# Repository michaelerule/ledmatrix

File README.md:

# LED matrix

Files related to hobby LED matrix display projects.

### License

Unless otherwise specified, media, text, and rendered outputs are licensed under the [Creative Commons Attribution Share Alike 4.0 license](https://choosealicense.com/licenses/cc-by-sa-4.0/) (CC BY-SA 4.0). Source code is licensed under the [GNU General Public License version 3.0](https://www.gnu.org/copyleft/gpl.html) (GPLv3). The CC BY-SA 4.0 is [one-way compatible](https://creativecommons.org/compatiblelicenses) with the GPLv3 license. 
This license does not apply to the project as a whole, but only to those modules or functions for which an alternative license is not otherwise specified.

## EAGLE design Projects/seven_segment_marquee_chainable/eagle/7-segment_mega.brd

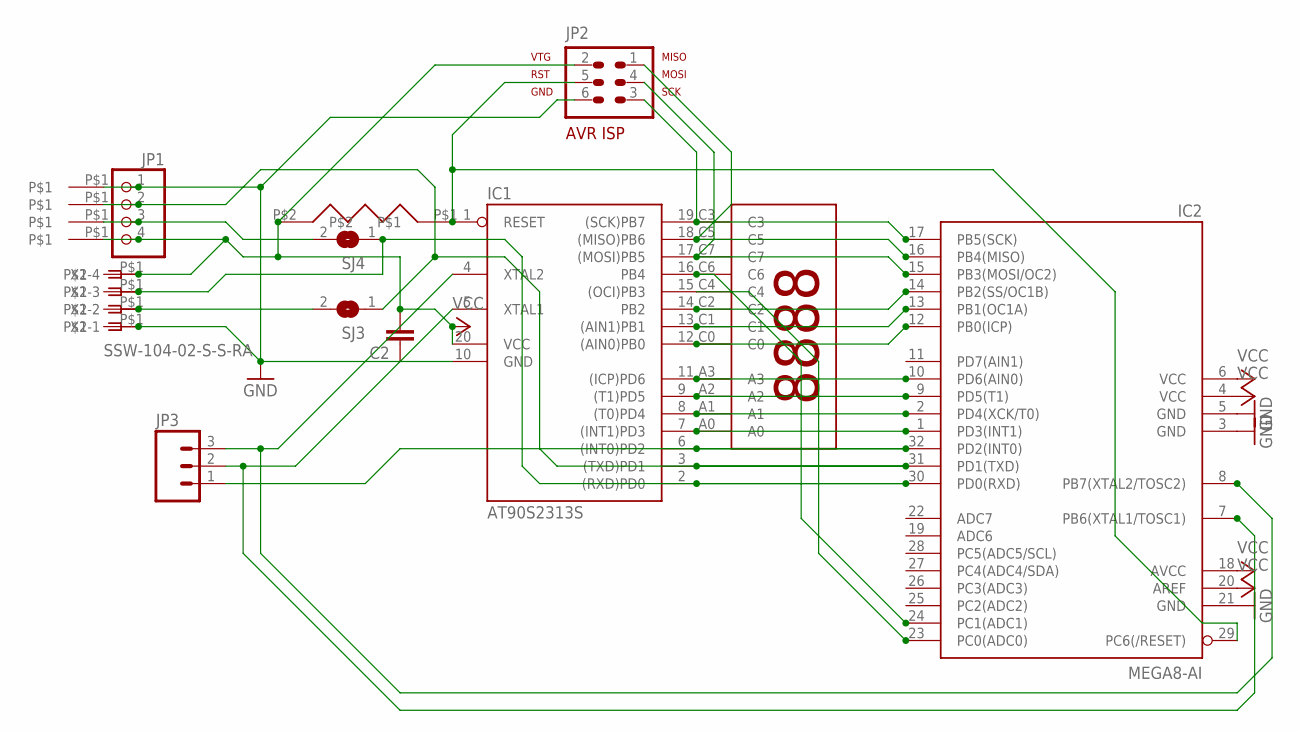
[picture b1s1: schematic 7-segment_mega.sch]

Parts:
C2: CAPPTH; CAP-PTH-SMALL
IC1: AT90S2313S; SO20L
IC2: MEGA8-AI; TQFP32-08
JP1: PINHD-1X4/90; 1X04/90
JP2: AVR-ISP-6
JP3: M03PTH; 1X03
SJ3, SJ4: SJ
U$1: 7-SEGMENT-DISPLAY-5462-BS; 7SEG_5462BS
U$2: R-6
U$3, U$4, U$5, U$6, U$7, U$8, U$9, U$10: WIREPAD_SQUARE_1
X2: SSW-104-02-S-S-RA

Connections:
GND: C2.1, IC1.10 (GND), IC2.3 (GND), IC2.5 (GND), IC2.21 (GND), JP1.1, JP2.6, U$3.P$1, U$10.P$1, X2.1
unnamed: IC1.14 (PB2), IC2.14 (PB2(SS/OC1B)), U$1.C2
unnamed: IC1.17 ((MOSI)PB5), IC2.15 (PB3(MOSI/OC2)), JP2.4, U$1.C7
unnamed: IC1.18 ((MISO)PB6), IC2.16 (PB4(MISO)), JP2.1, U$1.C5
unnamed: IC1.19 ((SCK)PB7), IC2.17 (PB5(SCK)), JP2.3, U$1.C3
unnamed: IC1.11 ((ICP)PD6), IC2.10 (PD6(AIN0)), U$1.A3
unnamed: IC1.7 ((INT1)PD3), IC2.1 (PD3(INT1)), U$1.A0
unnamed: IC1.12 ((AIN0)PB0), IC2.12 (PB0(ICP)), U$1.C0
unnamed: IC1.8 ((T0)PD4), IC2.2 (PD4(XCK/T0)), U$1.A1
unnamed: IC1.9 ((T1)PD5), IC2.9 (PD5(T1)), U$1.A2
unnamed: IC1.13 ((AIN1)PB1), IC2.13 (PB1(OC1A)), U$1.C1
unnamed: SJ3.2, U$9.P$1, X2.2
unnamed: JP1.3, SJ4.2, U$5.P$1
unnamed: IC1.2 ((RXD)PD0), IC2.30 (PD0(RXD)), SJ4.1, U$8.P$1, X2.3
unnamed: IC1.1 (RESET), IC2.29 (PC6(/RESET)), JP2.5, U$2.P$1
unnamed: IC1.3 ((TXD)PD1), IC2.31 (PD1(TXD)), JP1.2, SJ3.1, U$4.P$1
unnamed: IC1.15 ((OCI)PB3), IC2.23 (PC0(ADC0)), U$1.C4
unnamed: IC1.16 (PB4), IC2.24 (PC1(ADC1)), U$1.C6
PD2: IC1.6 ((INT0)PD2), IC2.32 (PD2(INT0)), JP3.1
VCC: C2.2, IC1.20 (VCC), IC2.4 (VCC), IC2.6 (VCC), IC2.18 (AVCC), IC2.20 (AREF), JP1.4, JP2.2, U$2.P$2, U$6.P$1, U$7.P$1, X2.4
XTAL0: IC1.4 (XTAL2), IC2.8 (PB7(XTAL2/TOSC2)), JP3.3
XTAL1: IC1.5 (XTAL1), IC2.7 (PB6(XTAL1/TOSC1)), JP3.2

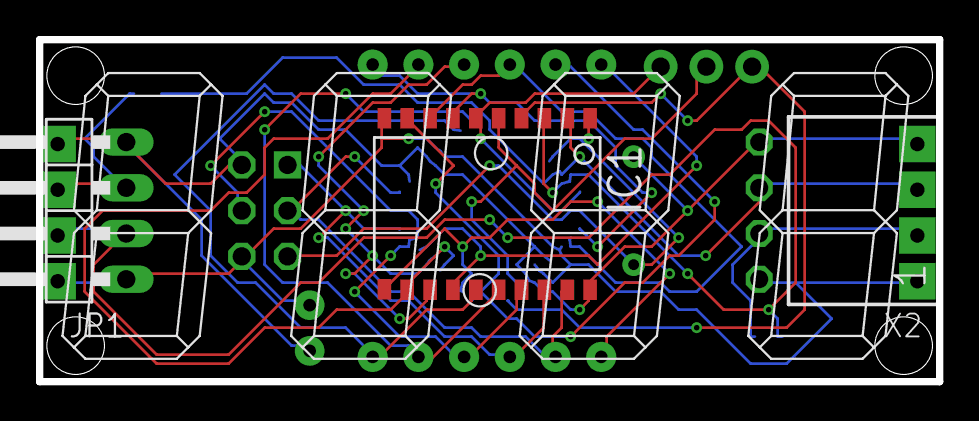
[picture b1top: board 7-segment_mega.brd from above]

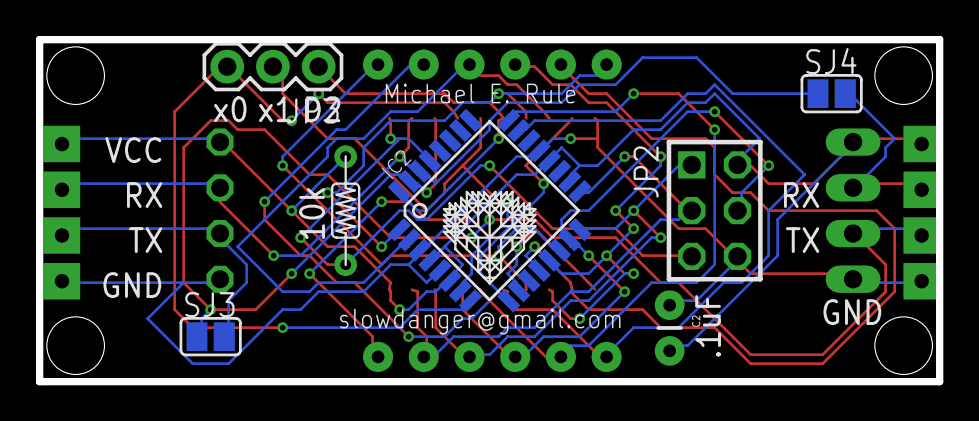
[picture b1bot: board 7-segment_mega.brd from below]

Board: 2 copper layers, 50.0 x 19.0 mm, 20 parts (8 on the bottom side), 22 nets.

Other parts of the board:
U$11: LOGO

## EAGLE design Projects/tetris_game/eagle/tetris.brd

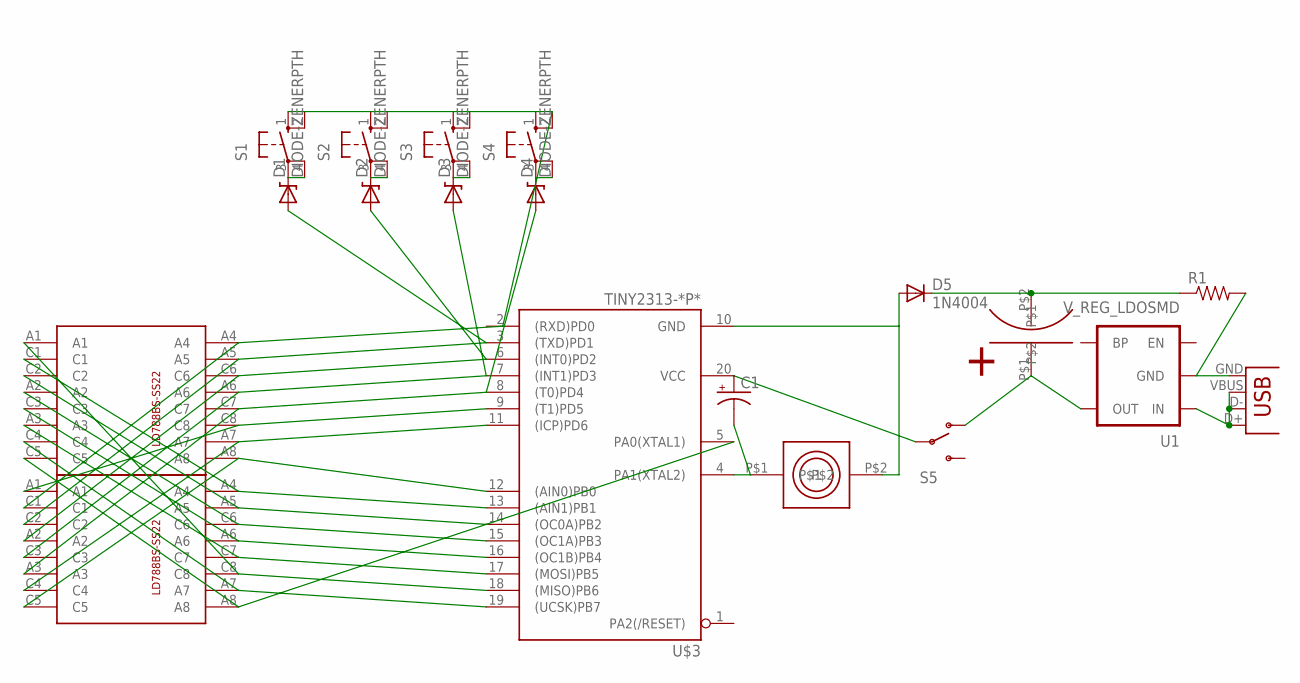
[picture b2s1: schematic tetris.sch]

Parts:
C1: CAP_POLPTH1; CPOL-RADIAL-100UF-25V
D1, D2, D3, D4: DIODE-ZENERPTH; DIODE-ZENER
D5: 1N4004; DO41-10
R1: RESISTORPTH1; AXIAL-0.3
S1, S2, S3, S4: 10-XX; B3F-10XX
S5: SWITCH-SPSTSMD2; SWITCH-SPDT-SMD
U1: V_REG_LDOSMD; SOT23-5
U$1, U$2: LD788BS-SS22
U$3: TINY2313-*P*; DIL20
U$4: I-80450RF; ISK4.1K_I-80450RF_I2G
U$5: NICHICON_12F; NICHICON_10X30
X1: USB-MICROB

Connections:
unnamed: U$1.A4, U$2.C1, U$3.13 ((AIN1)PB1)
unnamed: U$1.A5, U$2.C2, U$3.14 ((OC0A)PB2)
unnamed: U$1.C6, U$2.A2, U$3.15 ((OC1A)PB3)
unnamed: U$1.A6, U$2.C3, U$3.16 ((OC1B)PB4)
unnamed: U$1.C7, U$2.A3, U$3.17 ((MOSI)PB5)
unnamed: U$1.A7, U$2.C4, U$3.19 ((UCSK)PB7)
unnamed: U$1.A8, U$2.C5, U$3.5 (PA0(XTAL1))
unnamed: U$1.C8, U$2.A1, U$3.18 ((MISO)PB6)
unnamed: D5.C, R1.P$1 (1), U$5.P$2
unnamed: D1.P$2 (A), U$1.C2, U$2.A5, U$3.3 ((TXD)PD1)
unnamed: D2.P$2 (A), U$1.A2, U$2.C6, U$3.6 ((INT0)PD2)
unnamed: D3.P$2 (A), U$1.C3, U$2.A6, U$3.7 ((INT1)PD3)
unnamed: D4.P$2 (A), U$1.A3, U$2.C7, U$3.8 ((T0)PD4)
unnamed: U$1.A1, U$2.C8, U$3.9 ((T1)PD5)
unnamed: U$1.C4, U$2.A7, U$3.11 ((ICP)PD6)
unnamed: U$1.C5, U$2.A8, U$3.12 ((AIN0)PB0)
unnamed: C1.2 (-), U$3.4 (PA1(XTAL2)), U$4.P$1
unnamed: D5.A, U$3.10 (GND), U$4.P$2
unnamed: S5.1 (O), U1.5 (OUT), U$5.P$1
unnamed: D1.P$1 (C), S1.3, S1.4 (P1)
unnamed: D2.P$1 (C), S2.3, S2.4 (P1)
unnamed: D3.P$1 (C), S3.3, S3.4 (P1)
unnamed: D4.P$1 (C), S4.3, S4.4 (P1)
unnamed: R1.P$2 (2), U1.2 (GND), X1.GND
unnamed: U1.1 (IN), X1.D+, X1.D-, X1.VBUS
unnamed: C1.1 (+), S5.2, U$3.20 (VCC)
unnamed: S1.1 (S), S1.2 (S1), S2.1 (S), S2.2 (S1), S3.1 (S), S3.2 (S1), S4.1 (S), S4.2 (S1), U$1.C1, U$2.A4

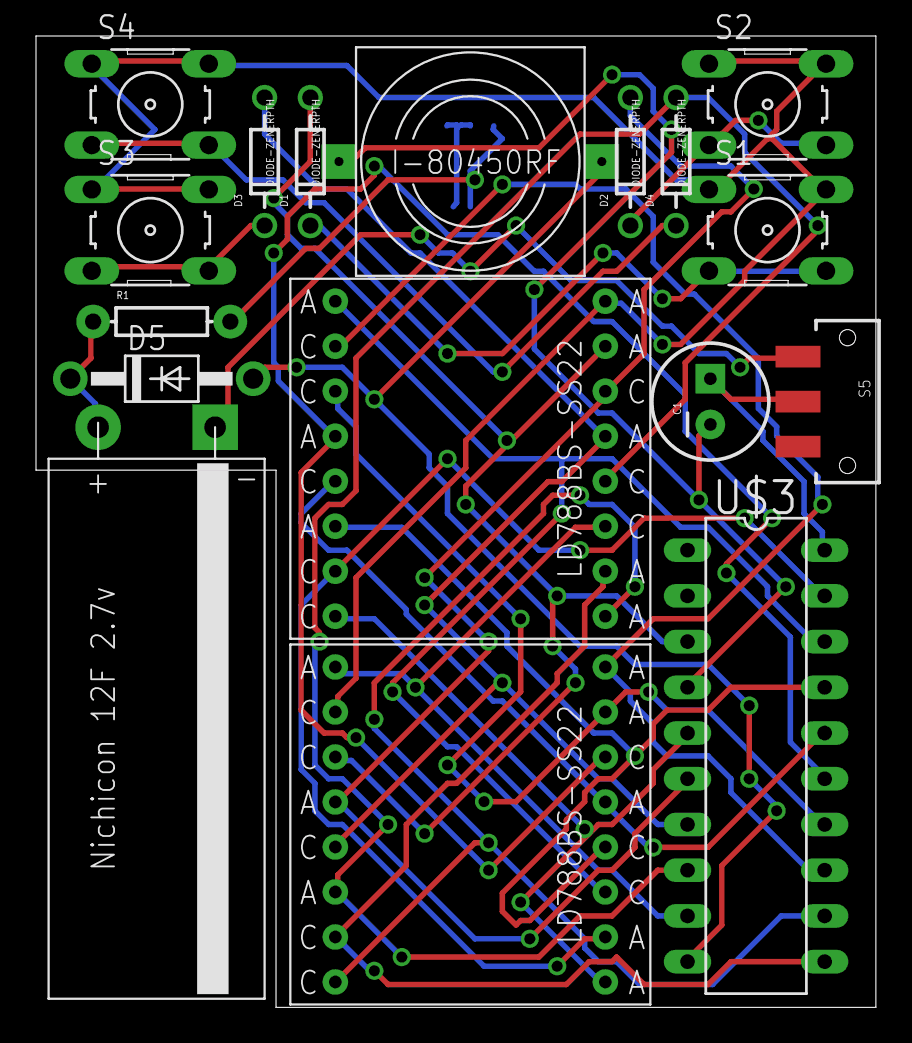
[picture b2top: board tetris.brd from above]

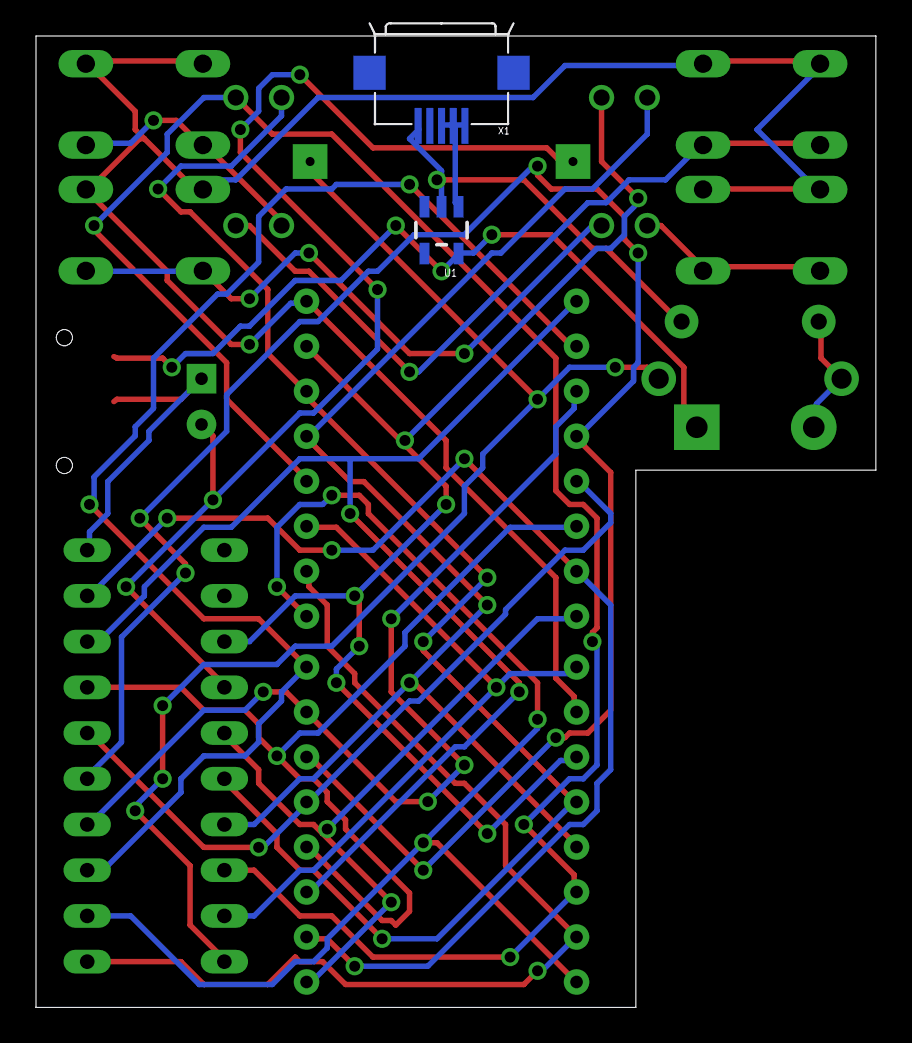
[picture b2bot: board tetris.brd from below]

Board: 2 copper layers, 46.7 x 54.0 mm, 19 parts (2 on the bottom side), 27 nets.

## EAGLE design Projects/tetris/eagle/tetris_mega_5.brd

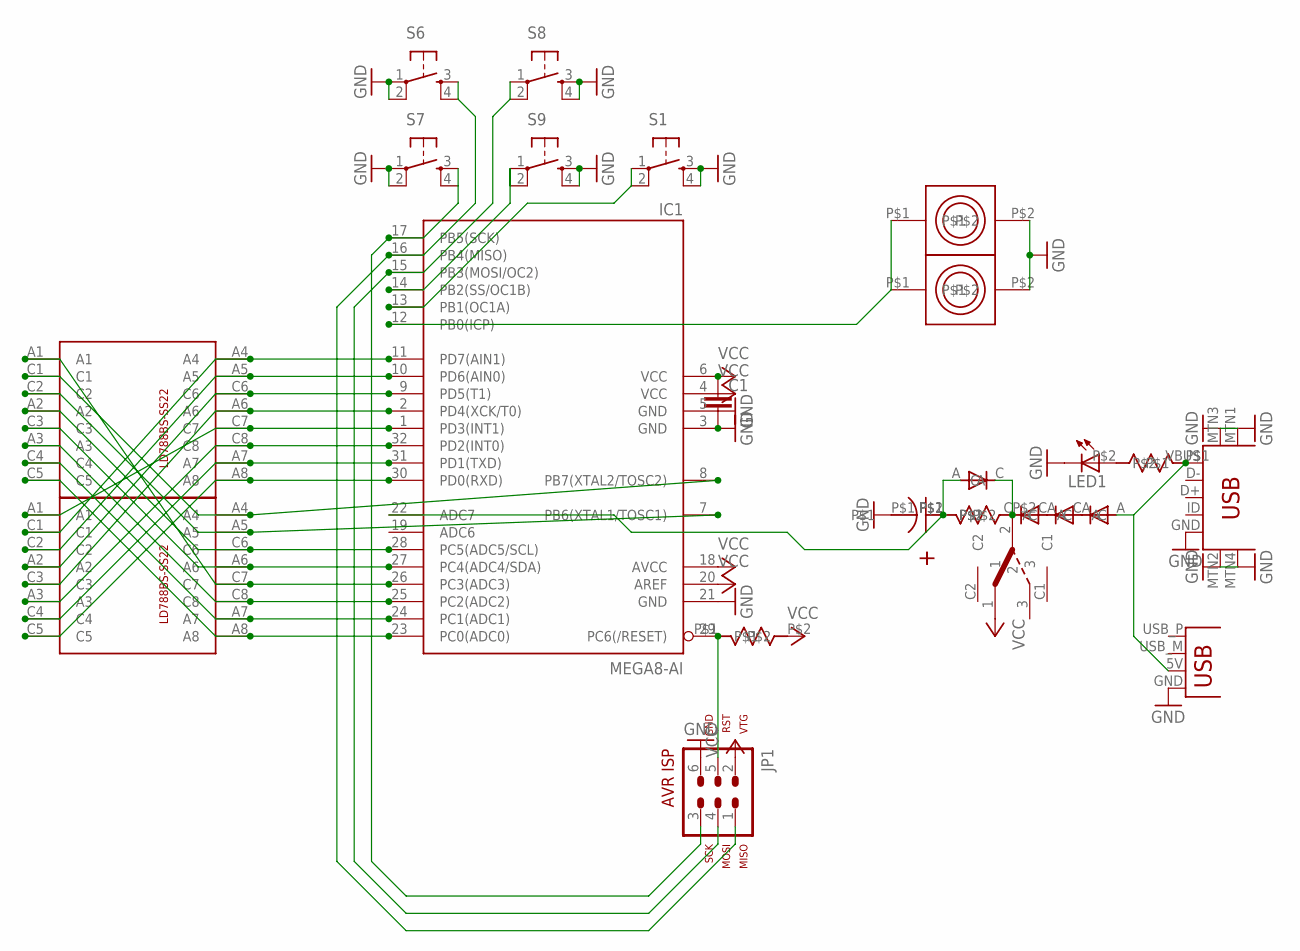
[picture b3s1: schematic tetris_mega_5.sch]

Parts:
C1: CAPPTH; CAP-PTH-SMALL
IC1: MEGA8-AI; TQFP32-08
JP1: AVR-ISP-6R
LED1: LED3MM
S1, S6, S7, S8, S9: TAC_SWITCHPTH; TACTILE-PTH
U$1, U$2: LD788BS-SS22
U$3: PIEZO_ROUND_PTH; PIEZO_ROUND_ENCASED_PTH
U$4: I-80450RF; ISK4.1K_I-80450RF_I2G
U$5: USB-MINIB-5PIN; USB-MINIB
U$6: NICHICON_12F; NICHICON_10X30
U$7, U$11, U$17: R-6
U$8, U$9, U$10, U$12: D-6; D-7.5
U$15: SPST_PTH; SWITCH2
X1: USBPCB; USB-A-PCB

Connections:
GND: C1.2, IC1.3 (GND), IC1.5 (GND), IC1.21 (GND), JP1.6, LED1.K (C), S1.3, S1.4, S6.1, S6.2, S7.1, S7.2, S8.3, S8.4, S9.3, S9.4, U$3.P$2, U$4.P$2, U$5.GND, U$5.MTN1 (MTN2), U$5.MTN2 (MTN3), U$5.MTN3 (MTN1), U$5.MTN4, U$6.P$1, X1.GND
unnamed: IC1.23 (PC0(ADC0)), U$1.A8, U$2.C5
unnamed: IC1.24 (PC1(ADC1)), U$1.A7, U$2.C4
unnamed: IC1.25 (PC2(ADC2)), U$1.C8, U$2.A3
unnamed: IC1.30 (PD0(RXD)), U$1.C5, U$2.A8
unnamed: IC1.31 (PD1(TXD)), U$1.C4, U$2.A7
unnamed: IC1.32 (PD2(INT0)), U$1.A3, U$2.C8
unnamed: IC1.8 (PB7(XTAL2/TOSC2)), U$1.A4, U$2.C1
unnamed: IC1.7 (PB6(XTAL1/TOSC1)), U$1.A5, U$2.C2
unnamed: IC1.28 (PC5(ADC5/SCL)), U$1.C6, U$2.A2
unnamed: IC1.27 (PC4(ADC4/SDA)), U$1.A6, U$2.C3
unnamed: IC1.11 (PD7(AIN1)), U$1.C1, U$2.A4
unnamed: IC1.10 (PD6(AIN0)), U$1.C2, U$2.A5
unnamed: IC1.9 (PD5(T1)), U$1.A2, U$2.C6
unnamed: IC1.2 (PD4(XCK/T0)), U$1.C3, U$2.A6
unnamed: IC1.1 (PD3(INT1)), U$1.A1, U$2.C7
unnamed: IC1.26 (PC3(ADC3)), U$1.C7, U$2.A1
unnamed: IC1.29 (PC6(/RESET)), JP1.5, U$7.P$1
unnamed: U$8.C, U$9.A
unnamed: U$9.C, U$10.A
unnamed: IC1.17 (PB5(SCK)), JP1.3
unnamed: IC1.16 (PB4(MISO)), JP1.1, S6.3, S6.4
unnamed: U$5.VBUS, U$8.A, U$17.P$1, X1.5V (VBUS)
unnamed: S9.1, S9.2
unnamed: S7.3, S7.4
unnamed: IC1.13 (PB1(OC1A)), S1.1, S1.2
unnamed: IC1.12 (PB0(ICP)), U$3.P$1, U$4.P$1
unnamed: U$10.C, U$11.P$2, U$12.C, U$15.2
unnamed: IC1.22 (ADC7), U$6.P$2, U$11.P$1, U$12.A
unnamed: LED1.A, U$17.P$2
unnamed: IC1.15 (PB3(MOSI/OC2)), JP1.4, S8.1, S8.2
VCC: C1.1, IC1.4 (VCC), IC1.6 (VCC), IC1.18 (AVCC), IC1.20 (AREF), JP1.2, U$7.P$2, U$15.1

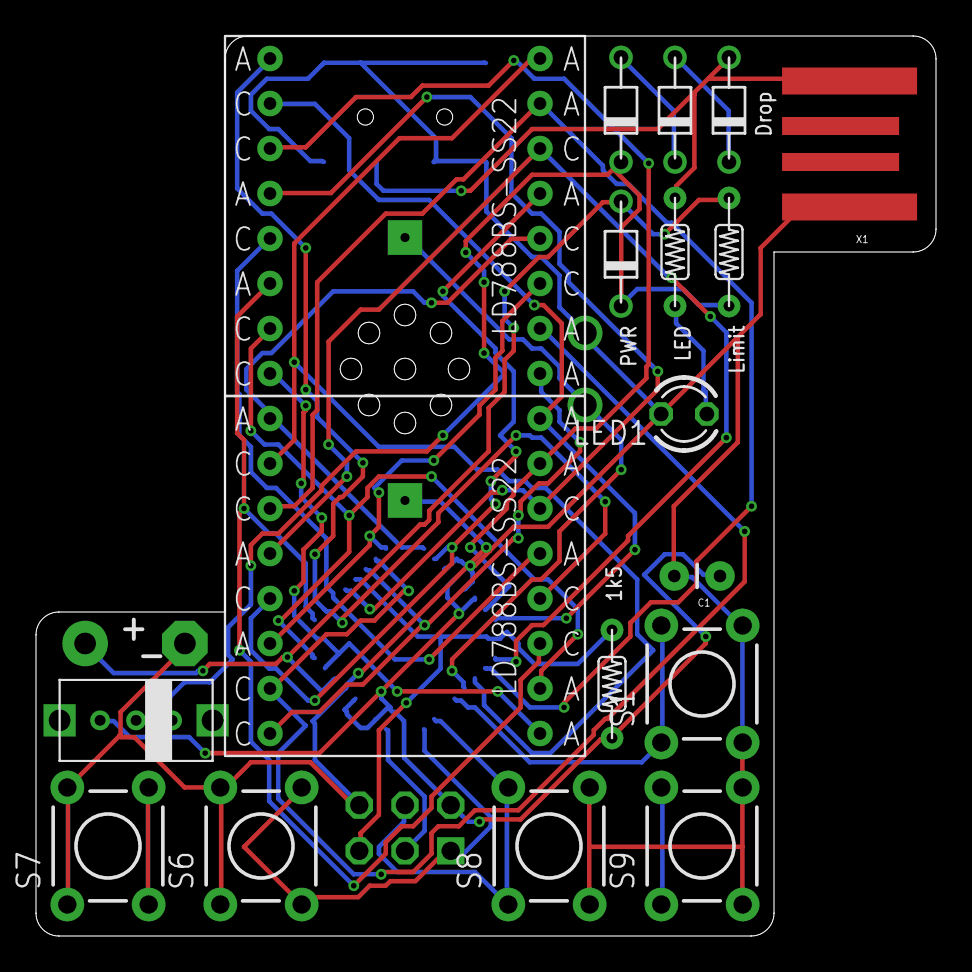
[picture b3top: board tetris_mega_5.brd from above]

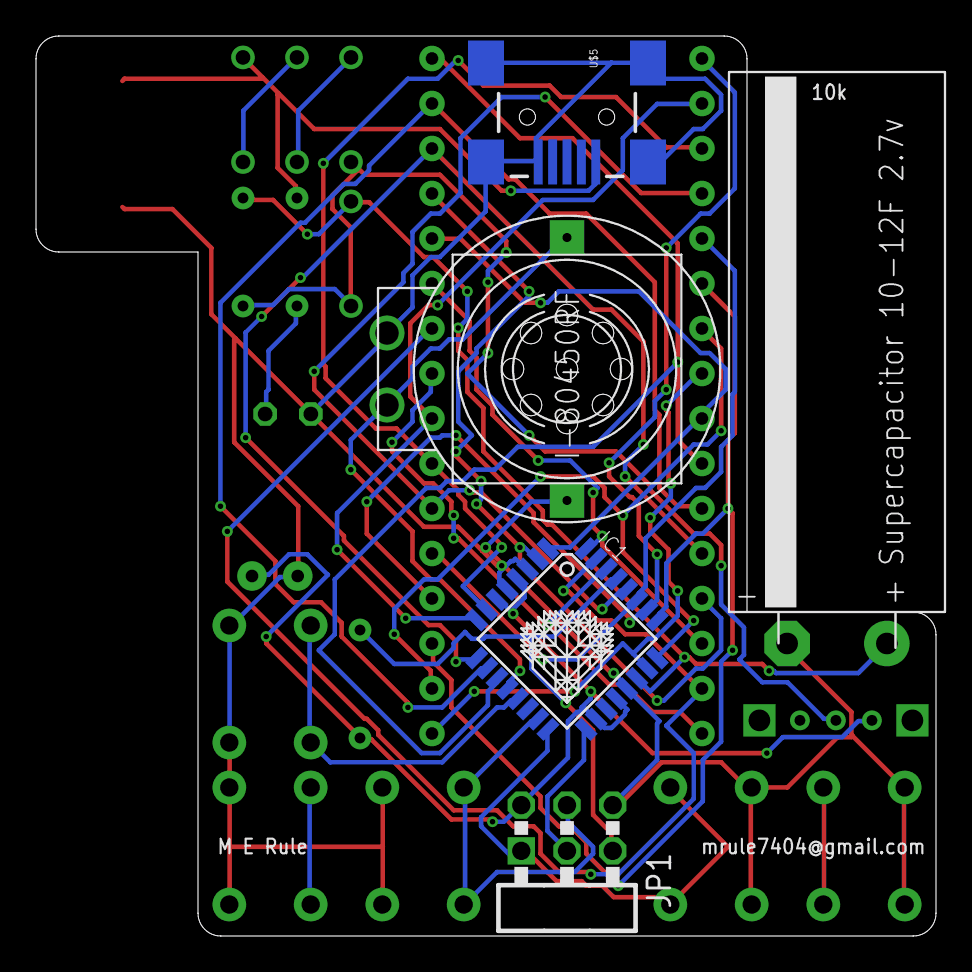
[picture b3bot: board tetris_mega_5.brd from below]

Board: 2 copper layers, 50.0 x 50.0 mm, 25 parts (7 on the bottom side), 32 nets.

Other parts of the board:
U$13: LOGO

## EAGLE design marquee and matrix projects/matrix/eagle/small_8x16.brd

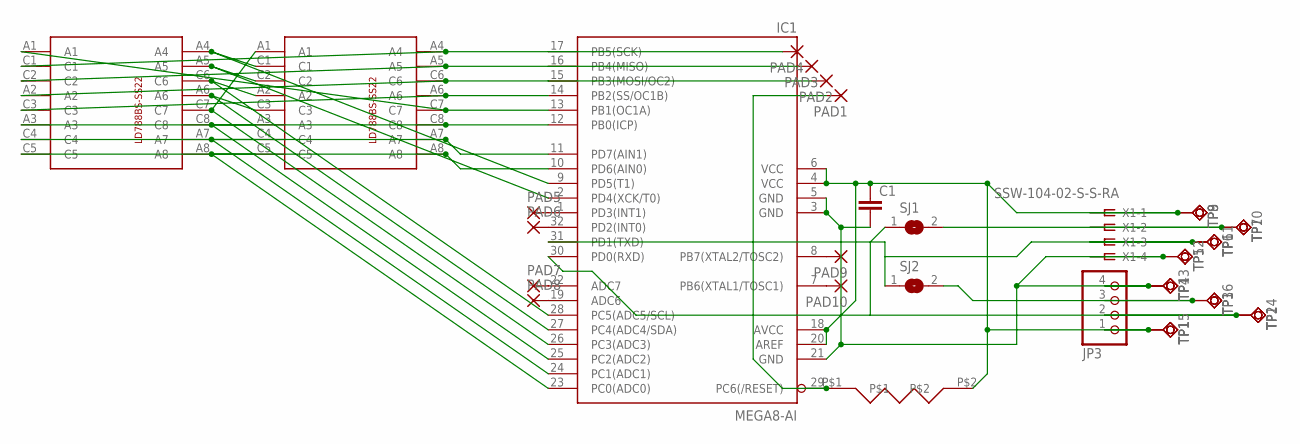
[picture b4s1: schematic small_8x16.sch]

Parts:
C1: CAPPTH; CAP-PTH-SMALL
IC1: MEGA8-AI; TQFP32-08
JP3: PINHD-1X4/90; 1X04/90
PAD1, PAD2, PAD3, PAD4, PAD5, PAD6, PAD7, PAD8, PAD9, PAD10: 1,6/0,8
SJ1, SJ2: SJ
TP1, TP2, TP3, TP4, TP5, TP6, TP7, TP8, TP9, TP10, TP11, TP12, TP13, TP14, TP15, TP16: TPSQTP20SQ; TP20SQ
U$1, U$2: LD788BS-SS22
U$3: R-6
X1: SSW-104-02-S-S-RA

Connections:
unnamed: IC1.24 (PC1(ADC1)), U$1.A7, U$2.C4
unnamed: IC1.25 (PC2(ADC2)), U$1.C8, U$2.A3
unnamed: IC1.26 (PC3(ADC3)), U$1.C7, U$2.A1
unnamed: IC1.27 (PC4(ADC4/SDA)), U$1.A6, U$2.C3
unnamed: IC1.28 (PC5(ADC5/SCL)), U$1.C6, U$2.A2
unnamed: IC1.2 (PD4(XCK/T0)), U$1.A5, U$2.C2
unnamed: IC1.9 (PD5(T1)), U$1.A4, U$2.C1
unnamed: IC1.15 (PB3(MOSI/OC2)), PAD2.1, U$1.A2, U$2.C6
unnamed: IC1.14 (PB2(SS/OC1B)), U$1.C3, U$2.A6
unnamed: IC1.13 (PB1(OC1A)), U$1.A1, U$2.C7
unnamed: IC1.12 (PB0(ICP)), U$1.A3, U$2.C8
unnamed: IC1.11 (PD7(AIN1)), U$1.C4, U$2.A7
unnamed: IC1.10 (PD6(AIN0)), U$1.C5, U$2.A8
unnamed: IC1.16 (PB4(MISO)), PAD3.1, U$1.C2, U$2.A5
unnamed: IC1.17 (PB5(SCK)), PAD4.1, U$1.C1, U$2.A4
unnamed: IC1.1 (PD3(INT1)), PAD5.1
unnamed: IC1.23 (PC0(ADC0)), U$1.A8, U$2.C5
unnamed: C1.2, IC1.3 (GND), IC1.5 (GND), IC1.21 (GND), JP3.4, TP4.TP, TP5.TP, TP12.TP, TP13.TP, X1.4
unnamed: C1.1, IC1.4 (VCC), IC1.6 (VCC), IC1.18 (AVCC), IC1.20 (AREF), JP3.1, TP1.TP, TP8.TP, TP9.TP, TP15.TP, U$3.P$2, X1.1
unnamed: IC1.32 (PD2(INT0)), PAD6.1
unnamed: SJ1.2, TP7.TP, TP10.TP, X1.2
unnamed: JP3.3, SJ2.2, TP3.TP, TP16.TP
unnamed: IC1.31 (PD1(TXD)), SJ2.1, TP6.TP, TP11.TP, X1.3
unnamed: IC1.30 (PD0(RXD)), JP3.2, SJ1.1, TP2.TP, TP14.TP
unnamed: IC1.29 (PC6(/RESET)), PAD1.1, U$3.P$1
unnamed: IC1.22 (ADC7), PAD7.1
unnamed: IC1.19 (ADC6), PAD8.1
unnamed: IC1.8 (PB7(XTAL2/TOSC2)), PAD9.1
unnamed: IC1.7 (PB6(XTAL1/TOSC1)), PAD10.1

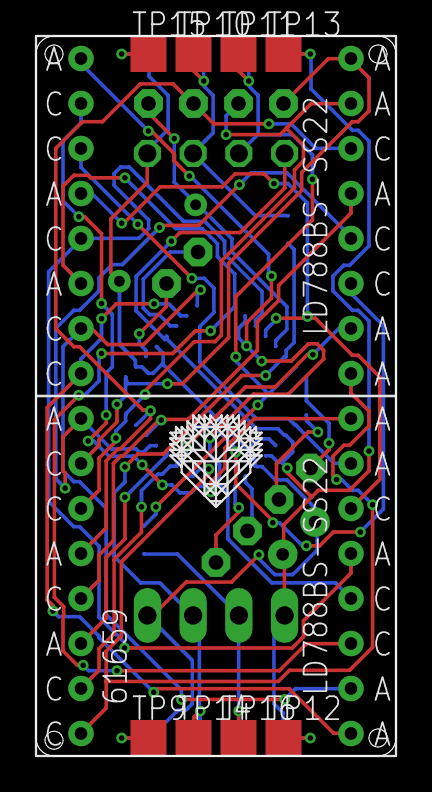
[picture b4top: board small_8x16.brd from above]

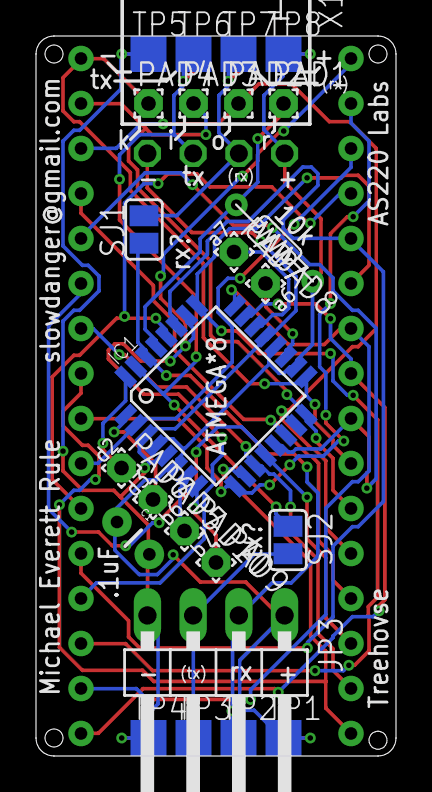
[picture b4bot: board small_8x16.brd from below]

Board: 2 copper layers, 20.0 x 40.0 mm, 36 parts (25 on the bottom side), 29 nets.

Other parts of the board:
U$4: LOGO

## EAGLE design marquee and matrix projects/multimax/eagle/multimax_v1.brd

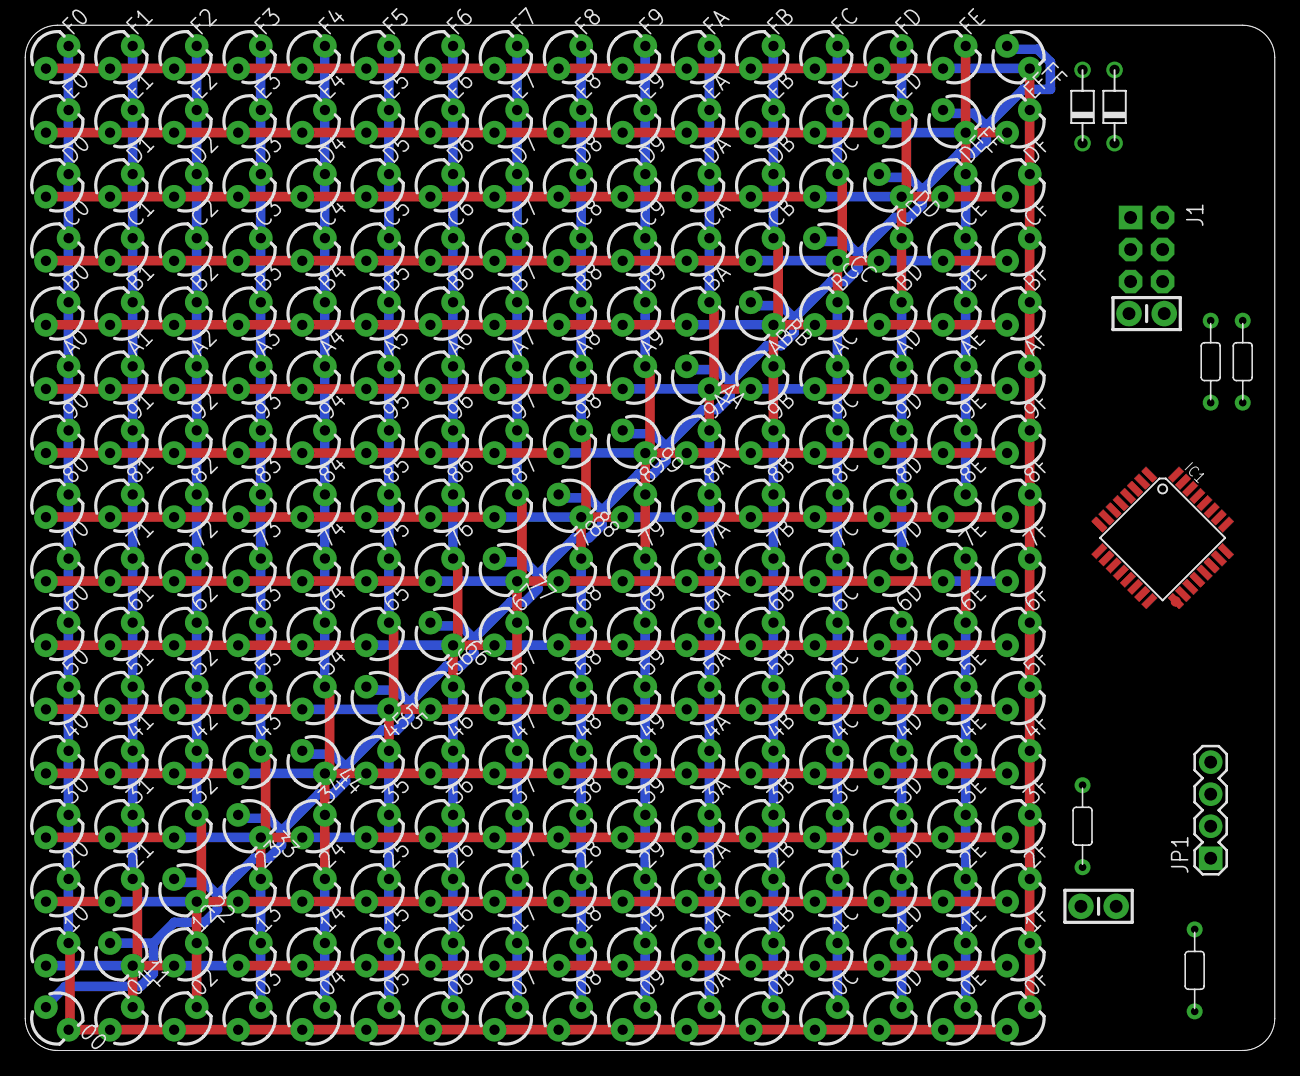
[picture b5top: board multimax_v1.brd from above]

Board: 2 copper layers, 99.1 x 81.3 mm, 267 parts (0 on the bottom side), 26 nets.

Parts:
00, 0A, 0B, 0C, 0D, 0E, 0F, 01, 1A, 1B, 1C, 1D, 1E, 1F, 02, 2A, 2B, 2C, 2D, 2E, 2F, 03, 3A, 3B, 3C, 3D, 3E, 3F, 04, 4A, 4B, 4C, 4D, 4E, 4F, 05, 5A, 5B, 5C, 5D, 5E, 5F, 06, 6A, 6B, 6C, 6D, 6E, 6F, 07, 7A, 7B, 7C, 7D, 7E, 7F, 08, 8A, 8B, 8C, 8D, 8E, 8F, 09, 9A, 9B, 9C, 9D, 9E, 9F, 10, 11, 12, 13, 14, 15, 16, 17, 18, 19, 20, 21, 22, 23, 24, 25, 26, 27, 28, 29, 30, 31, 32, 33, 34, 35, 36, 37, 38, 39, 40, 41, 42, 43, 44, 45, 46, 47, 48, 49, 50, 51, 52, 53, 54, 55, 56, 57, 58, 59, 60, 61, 62, 63, 64, 65, 66, 67, 68, 69, 70, 71, 72, 73, 74, 75, 76, 77, 78, 79, 80, 81, 82, 83, 84, 85, 86, 87, 88, 89, 90, 91, 92, 93, 94, 95, 96, 97, 98, 99: LED3MM
A0, A1, A2, A3, A4, A5, A6, A7, A8, A9: LED3MM
AA: LED3MM
AB: LED3MM
AC: LED3MM
AD: LED3MM
AE: LED3MM
AF: LED3MM
B0, B1, B2, B3, B4, B5, B6, B7, B8, B9: LED3MM
BA: LED3MM
BB: LED3MM
BC: LED3MM
BD: LED3MM
BE: LED3MM
BF: LED3MM
C0, C1, C2, C3, C4, C5, C6, C7, C8, C9: LED3MM
CA: LED3MM
CB: LED3MM
CC: LED3MM
CD: LED3MM
CE: LED3MM
CF: LED3MM
CP2, CP4: CAP-PTH-SMALL-KIT
D0, D1, D2, D3, D4, D5, D6, D7, D8, D9: LED3MM
DA: LED3MM
DB: LED3MM
DC: LED3MM
DD: LED3MM
DE: LED3MM
DF: LED3MM
E0, E1, E2, E3, E4, E5, E6, E7, E8, E9: LED3MM
EA: LED3MM
EB: LED3MM
EC: LED3MM
ED: LED3MM
EE: LED3MM
EF: LED3MM
F0, F1, F2, F3, F4, F5, F6, F7, F8, F9: LED3MM
FA: LED3MM
FB: LED3MM
FC: LED3MM
FD: LED3MM
FE: LED3MM
FF: LED3MM
IC1: MEGA8-AI; TQFP32-08
J1: AVR_SPI_PRG_6NS; 2X3-NS
JP1: 1X04
U$2, U$3, U$4, U$7: R-7
U$5, U$6: D-6; D-7.5

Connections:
D: 00.A, 11.A, 22.A, 33.A, 44.A, 55.A, 66.A, 77.A, 88.A, 99.A, AA.A, BB.A, CC.A, DD.A, EE.A, FF.A, IC1.8
GND: CP2.2, CP4.2, IC1.3, IC1.5, IC1.21, J1.6, JP1.4
unnamed: IC1.31, JP1.3
unnamed: IC1.30, JP1.2
unnamed: IC1.29, J1.5, U$2.P$2
unnamed: 0D.K, 1D.K, 2D.K, 3D.K, 4D.K, 5D.K, 6D.K, 7D.K, 8D.K, 9D.K, AD.K, BD.K, CD.K, D0.A, D1.A, D2.A, D3.A, D4.A, D5.A, D6.A, D7.A, D8.A, D9.A, DA.A, DB.A, DC.A, DD.K, DE.A, DF.A, ED.K, FD.K, IC1.16, J1.1
unnamed: IC1.1, U$4.P$1
unnamed: IC1.32, U$3.P$1
unnamed: 0F.K, 1F.K, 2F.K, 3F.K, 4F.K, 5F.K, 6F.K, 7F.K, 8F.K, 9F.K, AF.K, BF.K, CF.K, DF.K, EF.K, F0.A, F1.A, F2.A, F3.A, F4.A, F5.A, F6.A, F7.A, F8.A, F9.A, FA.A, FB.A, FC.A, FD.A, FE.A, FF.K, IC1.7
unnamed: 0B.K, 1B.K, 2B.K, 3B.K, 4B.K, 5B.K, 6B.K, 7B.K, 8B.K, 9B.K, AB.K, B0.A, B1.A, B2.A, B3.A, B4.A, B5.A, B6.A, B7.A, B8.A, B9.A, BA.A, BB.K, BC.A, BD.A, BE.A, BF.A, CB.K, DB.K, EB.K, FB.K, IC1.14
unnamed: 09.K, 9A.A, 9B.A, 9C.A, 9D.A, 9E.A, 9F.A, 19.K, 29.K, 39.K, 49.K, 59.K, 69.K, 79.K, 89.K, 90.A, 91.A, 92.A, 93.A, 94.A, 95.A, 96.A, 97.A, 98.A, 99.K, A9.K, B9.K, C9.K, D9.K, E9.K, F9.K, IC1.12
unnamed: 07.K, 7A.A, 7B.A, 7C.A, 7D.A, 7E.A, 7F.A, 17.K, 27.K, 37.K, 47.K, 57.K, 67.K, 70.A, 71.A, 72.A, 73.A, 74.A, 75.A, 76.A, 77.K, 78.A, 79.A, 87.K, 97.K, A7.K, B7.K, C7.K, D7.K, E7.K, F7.K, IC1.10
unnamed: 04.K, 4A.A, 4B.A, 4C.A, 4D.A, 4E.A, 4F.A, 14.K, 24.K, 34.K, 40.A, 41.A, 42.A, 43.A, 44.K, 45.A, 46.A, 47.A, 48.A, 49.A, 54.K, 64.K, 74.K, 84.K, 94.K, A4.K, B4.K, C4.K, D4.K, E4.K, F4.K, IC1.28
unnamed: 02.K, 2A.A, 2B.A, 2C.A, 2D.A, 2E.A, 2F.A, 12.K, 20.A, 21.A, 22.K, 23.A, 24.A, 25.A, 26.A, 27.A, 28.A, 29.A, 32.K, 42.K, 52.K, 62.K, 72.K, 82.K, 92.K, A2.K, B2.K, C2.K, D2.K, E2.K, F2.K, IC1.26
unnamed: U$3.P$2, U$5.A
unnamed: U$4.P$2, U$6.C, U$7.P$1
S0: 00.K, 0A.A, 0B.A, 0C.A, 0D.A, 0E.A, 0F.A, 01.A, 02.A, 03.A, 04.A, 05.A, 06.A, 07.A, 08.A, 09.A, 10.K, 20.K, 30.K, 40.K, 50.K, 60.K, 70.K, 80.K, 90.K, A0.K, B0.K, C0.K, D0.K, E0.K, F0.K, IC1.24
S1: 01.K, 1A.A, 1B.A, 1C.A, 1D.A, 1E.A, 1F.A, 10.A, 11.K, 12.A, 13.A, 14.A, 15.A, 16.A, 17.A, 18.A, 19.A, 21.K, 31.K, 41.K, 51.K, 61.K, 71.K, 81.K, 91.K, A1.K, B1.K, C1.K, D1.K, E1.K, F1.K, IC1.25
S3: 03.K, 3A.A, 3B.A, 3C.A, 3D.A, 3E.A, 3F.A, 13.K, 23.K, 30.A, 31.A, 32.A, 33.K, 34.A, 35.A, 36.A, 37.A, 38.A, 39.A, 43.K, 53.K, 63.K, 73.K, 83.K, 93.K, A3.K, B3.K, C3.K, D3.K, E3.K, F3.K, IC1.27
S5: 05.K, 5A.A, 5B.A, 5C.A, 5D.A, 5E.A, 5F.A, 15.K, 25.K, 35.K, 45.K, 50.A, 51.A, 52.A, 53.A, 54.A, 55.K, 56.A, 57.A, 58.A, 59.A, 65.K, 75.K, 85.K, 95.K, A5.K, B5.K, C5.K, D5.K, E5.K, F5.K, IC1.2
S6: 06.K, 6A.A, 6B.A, 6C.A, 6D.A, 6E.A, 6F.A, 16.K, 26.K, 36.K, 46.K, 56.K, 60.A, 61.A, 62.A, 63.A, 64.A, 65.A, 66.K, 67.A, 68.A, 69.A, 76.K, 86.K, 96.K, A6.K, B6.K, C6.K, D6.K, E6.K, F6.K, IC1.9
S8: 08.K, 8A.A, 8B.A, 8C.A, 8D.A, 8E.A, 8F.A, 18.K, 28.K, 38.K, 48.K, 58.K, 68.K, 78.K, 80.A, 81.A, 82.A, 83.A, 84.A, 85.A, 86.A, 87.A, 88.K, 89.A, 98.K, A8.K, B8.K, C8.K, D8.K, E8.K, F8.K, IC1.11
S10: 0A.K, 1A.K, 2A.K, 3A.K, 4A.K, 5A.K, 6A.K, 7A.K, 8A.K, 9A.K, A0.A, A1.A, A2.A, A3.A, A4.A, A5.A, A6.A, A7.A, A8.A, A9.A, AA.K, AB.A, AC.A, AD.A, AE.A, AF.A, BA.K, CA.K, DA.K, EA.K, FA.K, IC1.13
S12: 0C.K, 1C.K, 2C.K, 3C.K, 4C.K, 5C.K, 6C.K, 7C.K, 8C.K, 9C.K, AC.K, BC.K, C0.A, C1.A, C2.A, C3.A, C4.A, C5.A, C6.A, C7.A, C8.A, C9.A, CA.A, CB.A, CC.K, CD.A, CE.A, CF.A, DC.K, EC.K, FC.K, IC1.15, J1.4
S14: 0E.K, 1E.K, 2E.K, 3E.K, 4E.K, 5E.K, 6E.K, 7E.K, 8E.K, 9E.K, AE.K, BE.K, CE.K, DE.K, E0.A, E1.A, E2.A, E3.A, E4.A, E5.A, E6.A, E7.A, E8.A, E9.A, EA.A, EB.A, EC.A, ED.A, EE.K, EF.A, FE.K, IC1.17, J1.3
VCC: CP2.1, CP4.1, IC1.4, IC1.6, IC1.18, IC1.20, J1.2, JP1.1, U$2.P$1, U$7.P$2

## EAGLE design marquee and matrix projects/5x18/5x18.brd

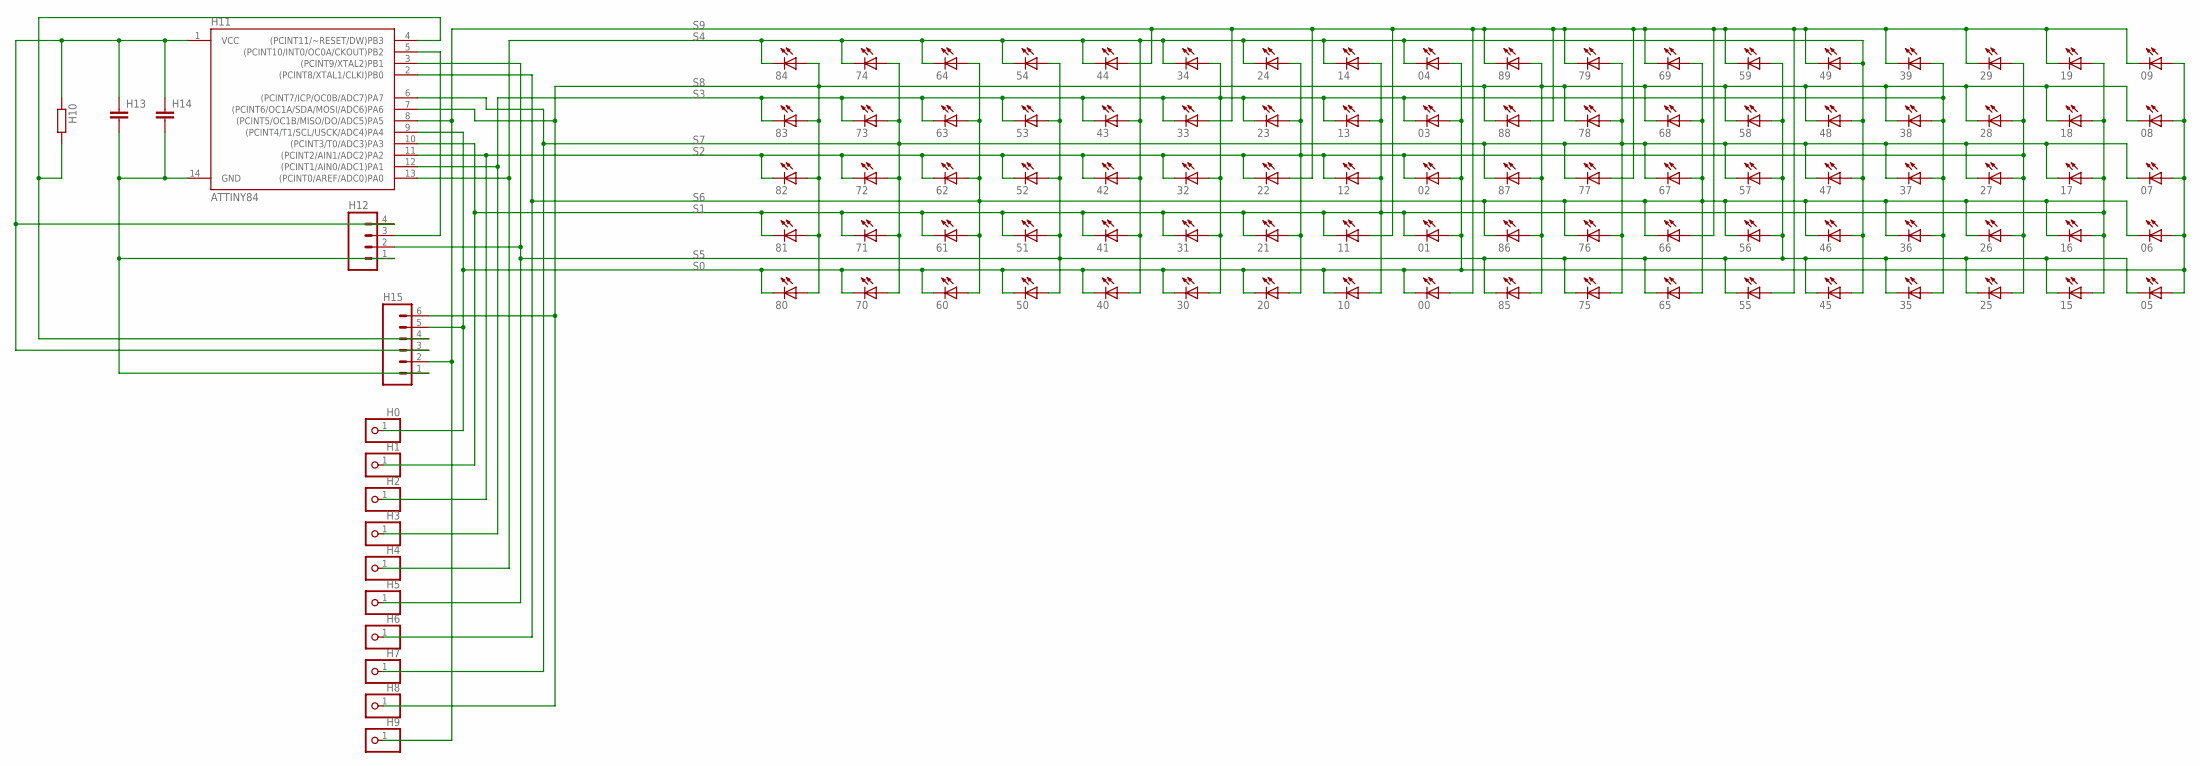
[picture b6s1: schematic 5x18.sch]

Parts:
00, 01, 02, 03, 04, 05, 06, 07, 08, 09, 10, 11, 12, 13, 14, 15, 16, 17, 18, 19, 20, 21, 22, 23, 24, 25, 26, 27, 28, 29, 30, 31, 32, 33, 34, 35, 36, 37, 38, 39, 40, 41, 42, 43, 44, 45, 46, 47, 48, 49, 50, 51, 52, 53, 54, 55, 56, 57, 58, 59, 60, 61, 62, 63, 64, 65, 66, 67, 68, 69, 70, 71, 72, 73, 74, 75, 76, 77, 78, 79, 80, 81, 82, 83, 84, 85, 86, 87, 88, 89: LED3MM
H0, H1, H2, H3, H4, H5, H6, H7, H8, H9: PINHD-1X1; 1X01
H10: R-EU_0204/7; 0204/7
H11: ATTINY84; SO14
H12: M04LOCK; 1X04_LOCK
H13, H14: C-EU050-025X075; C050-025X075
H15: M06LOCK; 1X06_LOCK

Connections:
S0: 00.K (C), 01.A, 02.A, 03.A, 04.A, 05.A, 06.A, 07.A, 08.A, 09.A, 10.K (C), 20.K (C), 30.K (C), 40.K (C), 50.K (C), 60.K (C), 70.K (C), 80.K (C), H0.1, H11.9 ((PCINT4/T1/SCL/USCK/ADC4)PA4), H15.5
S1: 01.K (C), 10.A, 11.K (C), 12.A, 13.A, 14.A, 15.A, 16.A, 17.A, 18.A, 19.A, 21.K (C), 31.K (C), 41.K (C), 51.K (C), 61.K (C), 71.K (C), 81.K (C), H1.1, H11.10 ((PCINT3/T0/ADC3)PA3)
S2: 02.K (C), 12.K (C), 20.A, 21.A, 22.K (C), 23.A, 24.A, 25.A, 26.A, 27.A, 28.A, 29.A, 32.K (C), 42.K (C), 52.K (C), 62.K (C), 72.K (C), 82.K (C), H2.1, H11.11 ((PCINT2/AIN1/ADC2)PA2)
S3: 03.K (C), 13.K (C), 23.K (C), 30.A, 31.A, 32.A, 33.K (C), 34.A, 35.A, 36.A, 37.A, 38.A, 39.A, 43.K (C), 53.K (C), 63.K (C), 73.K (C), 83.K (C), H3.1, H11.12 ((PCINT1/AIN0/ADC1)PA1)
S4: 04.K (C), 14.K (C), 24.K (C), 34.K (C), 40.A, 41.A, 42.A, 43.A, 44.K (C), 45.A, 46.A, 47.A, 48.A, 49.A, 54.K (C), 64.K (C), 74.K (C), 84.K (C), H4.1, H11.13 ((PCINT0/AREF/ADC0)PA0)
S5: 05.K (C), 15.K (C), 25.K (C), 35.K (C), 45.K (C), 50.A, 51.A, 52.A, 53.A, 54.A, 55.K (C), 56.A, 57.A, 58.A, 59.A, 65.K (C), 75.K (C), 85.K (C), H5.1, H11.3 ((PCINT9/XTAL2)PB1), H12.2
S6: 06.K (C), 16.K (C), 26.K (C), 36.K (C), 46.K (C), 56.K (C), 60.A, 61.A, 62.A, 63.A, 64.A, 65.A, 66.K (C), 67.A, 68.A, 69.A, 76.K (C), 86.K (C), H6.1, H11.2 ((PCINT8/XTAL1/CLKI)PB0)
S7: 07.K (C), 17.K (C), 27.K (C), 37.K (C), 47.K (C), 57.K (C), 67.K (C), 70.A, 71.A, 72.A, 73.A, 74.A, 75.A, 76.A, 77.K (C), 78.A, 79.A, 87.K (C), H7.1, H11.6 ((PCINT7/ICP/OC0B/ADC7)PA7)
S8: 08.K (C), 18.K (C), 28.K (C), 38.K (C), 48.K (C), 58.K (C), 68.K (C), 78.K (C), 80.A, 81.A, 82.A, 83.A, 84.A, 85.A, 86.A, 87.A, 88.K (C), 89.A, H8.1, H11.7 ((PCINT6/OC1A/SDA/MOSI/ADC6)PA6), H15.6
S9: 00.A, 09.K (C), 11.A, 19.K (C), 22.A, 29.K (C), 33.A, 39.K (C), 44.A, 49.K (C), 55.A, 59.K (C), 66.A, 69.K (C), 77.A, 79.K (C), 88.A, 89.K (C), H9.1, H11.8 ((PCINT5/OC1B/MISO/DO/ADC5)PA5), H15.2
S$1: H10.1, H11.1 (VCC), H12.4, H13.1, H14.1, H15.3
S$2: H10.2, H11.4 ((PCINT11/~RESET/DW)PB3), H15.4
S$3: H11.14 (GND), H12.1, H13.2, H14.2, H15.1
S$4: H11.5 ((PCINT10/INT0/OC0A/CKOUT)PB2), H12.3

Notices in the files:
parts and their libraries:
sparkFun: Licensing: CC v3.0 Share-Alike You are welcome to use this library for commercial purposes.
